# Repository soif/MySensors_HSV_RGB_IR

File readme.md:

# MySensors HSV RVB IR

This Arduino Sketch is a [MySensors](https://www.mysensors.org/) project to control an RGB let strip. It can be controlled using Mysensors messages (both HSV and RVB) , but still using a basic Infra Red remote. The sketch also reports temperature and luminosity using an LDR.

Please read the [description](description.md), for more information.

*Here is the [MySensors forums topic](http://forum.mysensors.org/topic/) about this project.*

## Disclaimer

**THIS PROJECT IS CURRENTLY AN APHA VERSION !** The sotware is mostly finished, and breadboard testing run fine, but the final Schematic and PCB is a work in progress...

## License

This program is free software; you can redistribute it and/or modify it under the terms of the GNU General Public License as published by the Free Software Foundation; either version 2 of the License, or (at your option) any later version.

This program is distributed in the hope that it will be useful, but WITHOUT ANY WARRANTY; without even the implied warranty of MERCHANTABILITY or FITNESS FOR A PARTICULAR PURPOSE.  See the GNU General Public License for more details.

You should have received a copy of the GNU General Public License along with this program; if not, write to the Free Software Foundation, Inc., 51 Franklin Street, Fifth Floor, Boston, MA 02110-1301 USA.

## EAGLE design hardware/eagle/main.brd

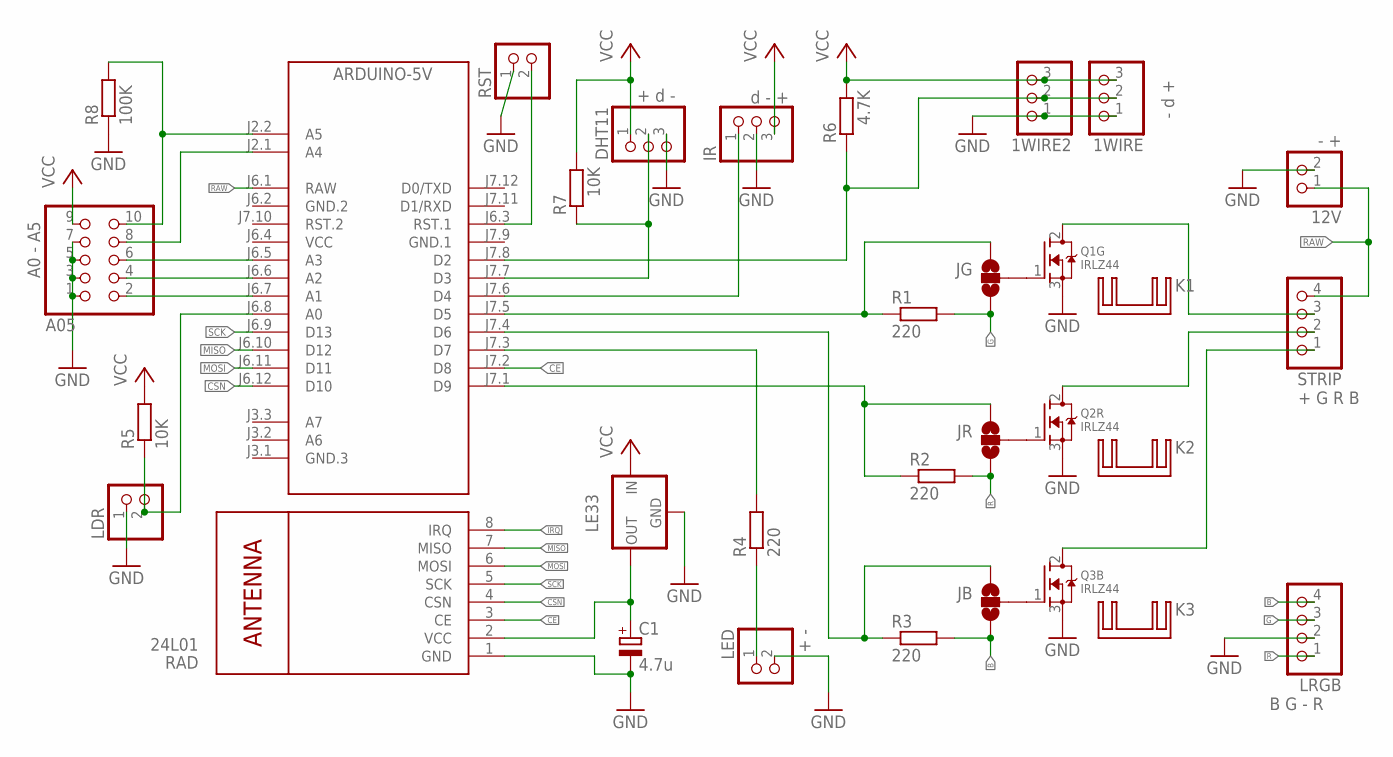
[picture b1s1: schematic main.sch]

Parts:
1WIRE: - d +; 1X03
1WIRE2: PINHD-1X3; 1X03
12V: - +; 1X02
A05: A0 - A5; 2X05
ARDUINO-5V: ARDUINO-PRO-MINI-5.0V#NP; ARDUINO-PRO-MINI#NP
C1: 4.7u; E5-6
DHT11: + d -; 1X03
IR: d - +; 1X03
JB: SOLDERJUMPER_2WAYS; SJ_3
JG: SOLDERJUMPER_2WAYS; SJ_3
JR: SOLDERJUMPER_2WAYS; SJ_3
K1, K2, K3: D02S
LDR: PINHD-1X2; 1X02
LE33: 79LXX
LED: + -; 1X02
LRGB: B G - R; 1X04
Q1G, Q2R, Q3B: IRLZ44; TO220V
R1, R2, R3, R4: 220; 0207/7
R5, R7: 10K; 0207/7
R6: 4.7K; 0207/7
R8: 100K; 0207/7
RAD: 24L01; WIRELESS-NRF24L01
RST: PINHD-1X2; 1X02
STRIP: + G R B; 1X04

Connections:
B: JB.3, LRGB.4, R3.2
CE: ARDUINO-5V.J7.2 (D8), RAD.3 (CE)
CSN: ARDUINO-5V.J6.12 (D10), RAD.4 (CSN)
G: JG.3, LRGB.3, R1.2
GND: 1WIRE.1, 1WIRE2.1, 12V.2, A05.1, A05.3, A05.5, A05.7, C1.-, DHT11.3, IR.2, LDR.1, LE33.GND, LED.2, LRGB.2, Q1G.3 (S), Q2R.3 (S), Q3B.3 (S), R8.1, RAD.1 (GND), RST.1
GND.1: ARDUINO-5V.J7.9 (GND.1)
GND.2: ARDUINO-5V.J6.2 (GND.2)
IRQ: RAD.8 (IRQ)
MISO: ARDUINO-5V.J6.10 (D12), RAD.7 (MISO)
MOSI: ARDUINO-5V.J6.11 (D11), RAD.6 (MOSI)
unnamed: JB.2, Q3B.1 (G)
unnamed: JR.2, Q2R.1 (G)
unnamed: JG.2, Q1G.1 (G)
unnamed: ARDUINO-5V.J7.1 (D9), JR.1, R2.1
unnamed: ARDUINO-5V.J7.4 (D6), JB.1, R3.1
unnamed: LED.1, R4.1
unnamed: ARDUINO-5V.J7.5 (D5), JG.1, R1.1
unnamed: A05.10, ARDUINO-5V.J2.2 (A5), R8.2
unnamed: A05.2, ARDUINO-5V.J6.7 (A1)
unnamed: A05.4, ARDUINO-5V.J6.6 (A2)
unnamed: Q1G.2 (D), STRIP.3
unnamed: Q3B.2 (D), STRIP.1
unnamed: Q2R.2 (D), STRIP.2
unnamed: 1WIRE.2, 1WIRE2.2, ARDUINO-5V.J7.8 (D2), R6.1
unnamed: ARDUINO-5V.J7.6 (D4), IR.1
unnamed: C1.+, LE33.OUT, RAD.2 (VCC)
unnamed: A05.6, ARDUINO-5V.J6.5 (A3)
unnamed: A05.8, ARDUINO-5V.J2.1 (A4)
unnamed: ARDUINO-5V.J6.8 (A0), LDR.2, R5.1
unnamed: ARDUINO-5V.J7.3 (D7), R4.2
unnamed: ARDUINO-5V.J7.7 (D3), DHT11.2, R7.1
unnamed: ARDUINO-5V.J6.3 (RST.1), RST.2
R: JR.3, LRGB.1, R2.2
RAW: 12V.1, ARDUINO-5V.J6.1 (RAW), STRIP.4
SCK: ARDUINO-5V.J6.9 (D13), RAD.5 (SCK)
VCC: 1WIRE.3, 1WIRE2.3, A05.9, ARDUINO-5V.J6.4 (VCC), DHT11.1, IR.3, LE33.IN, R5.2, R6.2, R7.2

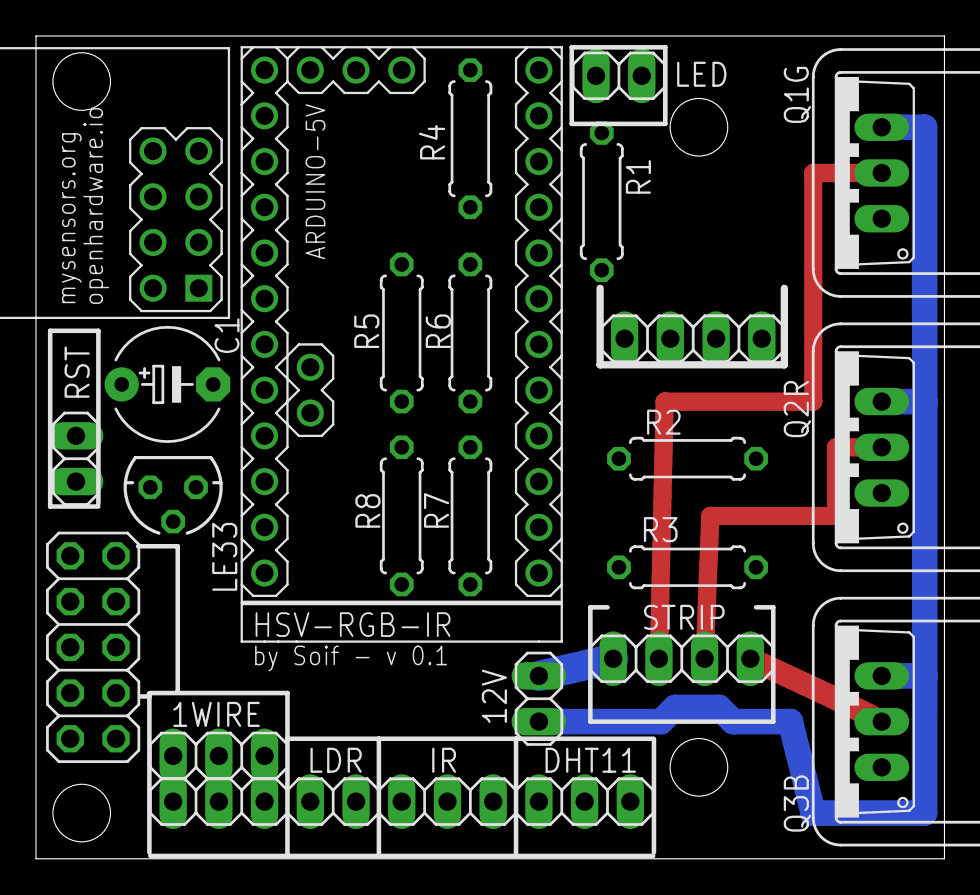
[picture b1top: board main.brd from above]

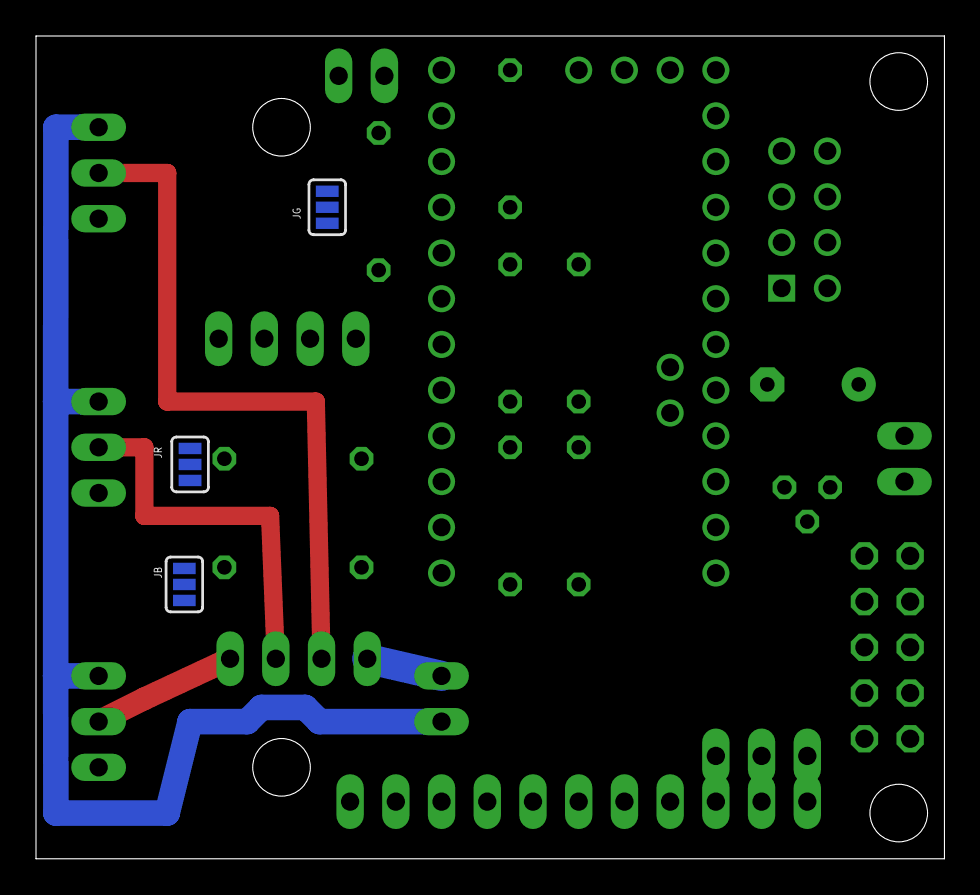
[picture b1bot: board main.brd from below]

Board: 2 copper layers, 50.5 x 45.7 mm, 32 parts (3 on the bottom side), 33 nets.

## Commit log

2016-02-13 Include required Libraries
2016-02-13 Status Led + FastLed rgb2hsv_approximate
2016-02-14 implements LDR + current_status + DimBright min 1
2016-02-14 rename file
2016-02-14 Optimize : hard-code Dallas conversion time (save 72 bytes )
2016-02-14 Optimize : cur_temp as int instead of float (save 504 bytes ) + comments
2016-02-14 Fix ConfirmFlash and ConfirmRGB (save 24 bytes) + Comments
2016-02-14 Renames functions
2016-02-14 Feedback State + define ACK + Color in EEprom + Ext. Debug (save 26 when Of, 1514! when Off)
2016-02-14 remove commented
2016-02-14 Add gizmocuz cool implode/explode example in comments
2016-02-14 Clean Comments
2016-02-14 Init mysensors.json description file
2016-02-14 rename Project
2016-02-14 reorder msg handling
2016-02-15 Reorder & rename Fn + lighten debug mess (save 500!)
2016-02-15 Receive true HSV data (sent as _RGB!) on child 2
2016-02-15 Fix Temperature decimal + retry temp faster when bugged + LDR ACK
2016-02-15 Repeater mode, comments cleanup
2016-02-21 add Eagle files
2016-02-21 latest schematic with eagle
2016-02-21 updated images for eagle project
2016-02-21 Playing with domoticz to see accepted messages
2016-02-21 Fix GH view
2016-02-21 Disclaimer : alpha
2017-03-13 typo

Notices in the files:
parts and their libraries:
diy-modules: Released under the Creative Commons Attribution 4.0 International License: http://creativecommons.org/licenses/by/4.0
MD-Passives: Licensing: CC v3.0 Share-Alike You are welcome to use this library for commercial purposes.
